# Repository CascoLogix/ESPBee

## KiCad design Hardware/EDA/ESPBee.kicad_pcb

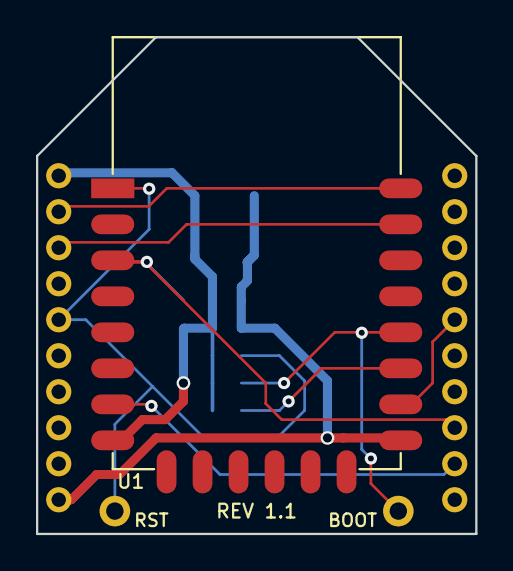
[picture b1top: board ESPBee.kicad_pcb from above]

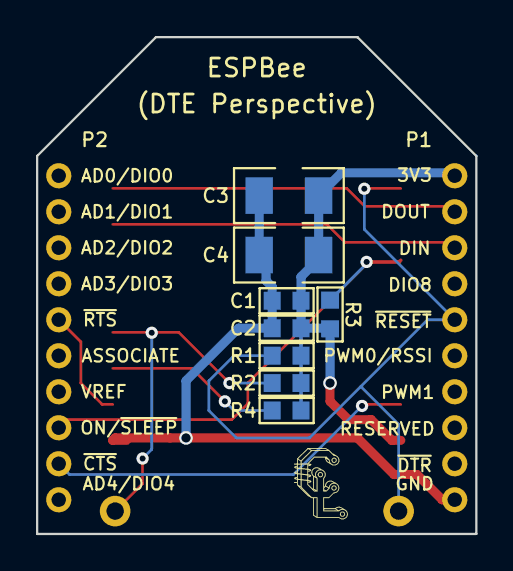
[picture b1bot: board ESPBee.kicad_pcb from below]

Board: 2 copper layers, 24.4 x 27.6 mm, 14 parts (11 on the bottom side), 10 nets.

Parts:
C1: 0.1uF; 0603
C2: 1uF; 0603
C3, C4: 47uF; 1206
G1: Casco_Logix_Logo; Casco_Logix_Logo_4x4MM
P1: XBEE HEADER; HEADER_XBEE_P1_P10_ALT3
P2: HEADER_M_XBEE_P11-P20_PTH_DTE; HEADER_XBEE_P11_P20_ALT3
R1, R2, R3, R4: 10K; R0603
TP1, TP2: TEST; WIRE_PAD_22AWG
U1: ESP-12E

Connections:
/~BOOTLOAD: R2.2, TP2.1, U1.18
/~RECOVERY: R4.2, U1.17
CTS: P2.12, U1.7
GND: C1.2, C2.2, C3.2, C4.2, P1.10, U1.15
ON/~SLEEP: P2.13, R3.2, U1.3
RST: P1.5, R1.2, TP1.1, U1.1
RTS: P2.16, U1.16
RXD: P1.3, U1.21
TXD: P1.2, U1.22
VDD: C1.1, C2.1, C3.1, C4.1, P1.1, R1.1, R2.1, R3.1, R4.1, U1.8

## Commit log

2016-11-29 First commit. Rev 0.1 ordered from OSHPark.
2017-02-18 Fixed connections and added pull-up/down resistors for configuration pins.
2017-02-20 Corrected links to 3D components in PCB file. Added footprints archive, shapes3D folder for archiving the STEP and WRL component models and added 3D MCAD of PCB assembly from KiCAD Stepup script.
2017-05-30 Updated schematic and board layout to include ON/SLEEP signal. Generated new gerber files.
2017-07-13 Removed silkscreen around header through holes and regenerated gerbers.
2017-07-30 Updated PCB title block. Generated PDF drawings of PCB. Re-arranged folder structure.
2017-07-30 Added media. Corrected name in schematic file.
2018-01-28 Added pinout diagram to repository
2018-02-17 Added test points for Boot and Reset signals. Cleaned up routing.
2018-12-23 Updated schematic per remapped schematic decals in KiCAD version 5.0.0.
